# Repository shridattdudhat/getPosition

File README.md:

## Welcome to GitHub Pages

You can use the [editor on GitHub](https://github.com/shridattdudhat/getPosition/edit/master/README.md) to maintain and preview the content for your website in Markdown files.

Whenever you commit to this repository, GitHub Pages will run [Jekyll](https://jekyllrb.com/) to rebuild the pages in your site, from the content in your Markdown files.

### Markdown

Markdown is a lightweight and easy-to-use syntax for styling your writing. It includes conventions for

```markdown
Syntax highlighted code block

# Header 1
## Header 2
### Header 3

- Bulleted
- List

1. Numbered
2. List

**Bold** and _Italic_ and `Code` text

[Link](url) and 
```

For more details see [GitHub Flavored Markdown](https://guides.github.com/features/mastering-markdown/).

### Jekyll Themes

Your Pages site will use the layout and styles from the Jekyll theme you have selected in your [repository settings](https://github.com/shridattdudhat/getPosition/settings). The name of this theme is saved in the Jekyll `_config.yml` configuration file.

### Support or Contact

Having trouble with Pages? Check out our [documentation](https://help.github.com/categories/github-pages-basics/) or [contact support](https://github.com/contact) and we’ll help you sort it out.

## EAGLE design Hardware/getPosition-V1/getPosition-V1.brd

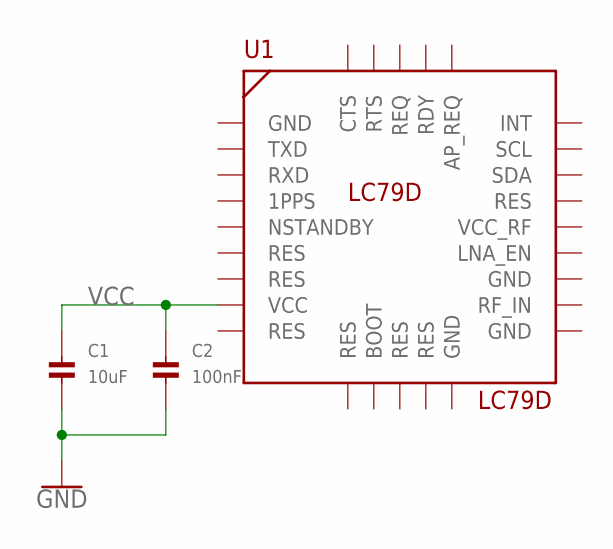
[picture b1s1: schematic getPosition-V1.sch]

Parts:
C1: 10uF; 0805
C2: 100nF; 0805
U1: LC79D

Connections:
GND: C1.2, C2.2
VCC: C1.1, C2.1, U1.VCC

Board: 2 copper layers, 3 parts (0 on the bottom side), 2 nets, no tracks yet.

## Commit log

2020-06-29 Set theme jekyll-theme-cayman
2020-07-01 kicad and eagle
2020-07-17 KiCad Project for getPosition
2020-10-31 Update fp-info-cache
2021-07-27 Create LICENSE

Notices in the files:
parts and their libraries:
microbuilder: This work is placed in the public domain, and may be freely used for commercial and non-commercial work with the following conditions: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
SparkFun-PowerSymbols: Licensing: Creative Commons ShareAlike 4.0 International - https://creativecommons.org/licenses/by-sa/4.0
